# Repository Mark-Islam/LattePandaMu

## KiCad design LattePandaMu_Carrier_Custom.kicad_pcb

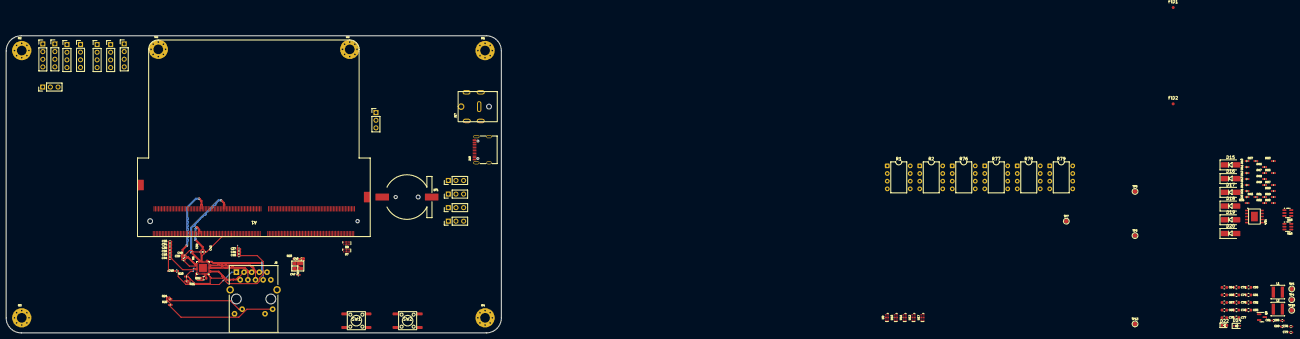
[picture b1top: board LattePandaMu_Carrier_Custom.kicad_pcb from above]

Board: 4 copper layers, 164.3 x 98.6 mm, 127 parts (0 on the bottom side), 90 nets.

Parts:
A1: LattePanda_Mu; LattePanda_Module_H8.0mm_Horizontal
BT1: Battery_Cell; Battery_Holder_CR1220_S8411-45R
C33, C34, C35, C36, C37, C38, C39, C40, C41, C42, C43, C45, C48: 100nF/50V; C_0402_1005Metric
C44: 10uF/50V; C_0402_1005Metric
C46, C47: 12pF/50V; C_0402_1005Metric
C61, C66, C69: 1uF/16V; C_0402_1005Metric
C64, C65, C67, C68, C74, C75, C76, C77, C80, C81, C82, C83: 22uF/10V; C_0603_1608Metric
C70, C71: 100nF/50V; C_0603_1608Metric
C78, C79: 100nF/16V; C_0402_1005Metric
D10, D11, D21, D25: ESD9B5.0ST5G; D_0402_1005Metric
D12, D13, D14: D_Zener; D_0402_1005Metric
D15, D16, D17, D18, D19, D20: D_Schottky; D_SMA
D22: LED; LED_0603_1608Metric
D24: 3V3 Izt=5mA; D_SOD-323
FID1, FID2: Fiducial; Fiducial_1mm_Mask2mm
H1, H2, H3, H4, H5, H6: MountingHole_Pad; MountingHole_3.2mm_M3_Pad_Via
J1, J8, J10, J11, J14: Conn_01x03_Pin; PinHeader_1x03_P2.54mm_Vertical
J6: RJ45_RB1-125B8G1A; RJ45_UDE_RB1-125B8G1A
J7, J9, J12, J13, J19, J20, J21: Conn_01x04; PinHeader_1x04_P2.54mm_Vertical
J17: Barrel_Jack_Switch; DC_Jack_DC007B_30V_10A
J18: USB_C_Receptacle_USB2.0_16P; USB_C_Receptacle_G-Switch_GT-USB-7010ASV
JP1: Jumper_3_Bridged12; PinHeader_1x03_P2.54mm_Vertical
L1, L2: 2.2uH/4.3A; L_Sunlord_SWPA4020S
Q8: 2N7002; SOT-23
R1: 1K/1%; DIP-8_W7.62mm
R2, R78, R79: 10K/1%; DIP-8_W7.62mm
R20, R21, R36, R49, R58: 10K/1%; R_0402_1005Metric
R22: 2.49K/1%; R_0603_1608Metric
R23: 1M/1%; R_0402_1005Metric
R24, R25: 470R/1%; R_0402_1005Metric
R37, R47: 1K/1%; R_0402_1005Metric
R43: 56K/1%; R_0402_1005Metric
R46, R48, R55: 100R/1%; R_0402_1005Metric
R51: 100K/1%; R_0402_1005Metric
R52, R53: 2.2K/1%; R_0402_1005Metric
R57: 75K/1%; R_0402_1005Metric
R59: 21.5K/1%; R_0402_1005Metric
R60: 4.7K/1%; R_0402_1005Metric
R76, R77: 100K/1%; DIP-8_W7.62mm
SW1, SW2: SW_Push; SW_Push_6x6x6
TP3, TP4, TP5, TP6, TP7, TP10, TP13: TestPoint; TestPoint_Pad_D1.5mm
U6: RTL8111H-CG-RH; QFN-32-1EP_4x4mm_P0.4mm_EP2.65x2.65mm
U7, U8, U9, U10, U11, U12, U17: D3V3XA4B10LP; Diodes_UDFN-10_1.0x2.5mm_P0.5mm
U14: USB PD等快充协议受电芯片-CH224K-ESSOP10; ESSOP-10-1EP_3.9x5mm_P1.0mm_EP3.2x2.3
U15, U16: LM2734X; TSOT-23-6
Y1: 25MHz; Crystal_SMD_3225-4Pin_3.2x2.5mm

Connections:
+1V0: C33.2, C34.2, C35.2, C36.2, C40.2, C44.2, U6.3 (AVDD10), U6.8 (AVDD10), U6.22 (DVDD10), U6.24 (REGOUT), U6.30 (AVDD10)
+3V3: C37.2, C41.2, C45.2, C75.2, C77.2, C79.2, C81.2, C83.2, J13.1, J13.2, J13.3, J13.4, J14.1, J14.2, J14.3, J21.1, J21.2, J21.3, J21.4, L2.2, R20.2, R21.2, R24.2, R25.2, R52.1, R59.2, TP6.1 (1_1), U6.11 (AVDD33), U6.23 (VDDREG), U6.32 (AVDD33)
+5V: C74.2, C76.2, C78.2, C82.2, L1.2, R57.2, TP5.1 (1_1)
+12V: D15.2 (A), D16.2 (A), D17.2 (A), J17.1, TP4.1 (1_1)
+15V: D12.1 (K), D18.2 (A), D19.2 (A), D20.2 (A), J18.A4 (VBUS), J18.A9 (VBUS), J18.B4 (VBUS), J18.B9 (VBUS), R36.1, R37.1, TP3.1 (1_1)
+BATT: A1.115 (VBAT), R1.2
/GPIO/GPP_D0: A1.128 (GPP_D0), J19.1, U17.1, U17.10 (NC)
/GPIO/GPP_D1: A1.130 (GPP_D1), J19.2, U17.2, U17.9 (NC)
/GPIO/GPP_D2: A1.132 (GPP_D2), J19.3, U17.4, U17.7 (NC)
/GPIO/GPP_D3: A1.134 (GPP_D3), J19.4, U17.5, U17.6 (NC)
/GPIO/I2C2_SCL: A1.154 (I2C2_SCL), J9.1, U11.1, U11.10 (NC)
/GPIO/I2C2_SDA: A1.156 (I2C2_SDA), J7.1, U9.1, U9.10 (NC)
/GPIO/I2C3_SCL: A1.150 (I2C3_SCL), J9.2, U11.2, U11.9 (NC)
/GPIO/I2C3_SDA: A1.152 (I2C3_SDA), J7.2, U9.2, U9.9 (NC)
/GPIO/I2C4_SCL: A1.146 (I2C4_SCL), J9.3, U11.4, U11.7 (NC)
/GPIO/I2C4_SDA: A1.148 (I2C4_SDA), J7.3, U9.4, U9.7 (NC)
/GPIO/I2C5_SCL: A1.142 (I2C5_SCL), J9.4, U11.5, U11.6 (NC)
/GPIO/I2C5_SDA: A1.144 (I2C5_SDA), J7.4, U9.5, U9.6 (NC)
/GPIO/SOC_UART0_RX: A1.137 (UART0_RXD), J8.1, U10.1, U10.10 (NC)
/GPIO/SOC_UART0_TX: A1.139 (UART0_TXD), J10.1, U12.1, U12.10 (NC)
/GPIO/SOC_UART1_RX: A1.141 (UART1_RXD), J8.2, U10.2, U10.9 (NC)
/GPIO/SOC_UART1_TX: A1.143 (UART1_TXD), J10.2, U12.2, U12.9 (NC)
/GPIO/SOC_UART2_RX: A1.140 (UART2_RXD), J8.3, U10.4, U10.7 (NC)
/GPIO/SOC_UART2_TX: A1.138 (UART2_TXD), J10.3, U12.4, U12.7 (NC)
/Gigabit Ethernet/GbE_PCIe_CLK+: A1.94 (REFCLK4+), U6.15 (REFCLK_P)
/Gigabit Ethernet/GbE_PCIe_CLK-: A1.96 (REFCLK4-), U6.16 (REFCLK_N)
/Gigabit Ethernet/GbE_PCIe_RX+: A1.64 (HSIO6_RX+), C43.2
/Gigabit Ethernet/GbE_PCIe_RX-: A1.66 (HSIO6_RX-), C39.2
/Gigabit Ethernet/GbE_PCIe_TX+: A1.61 (HSIO6_TX+), C42.2
/Gigabit Ethernet/GbE_PCIe_TX-: A1.63 (HSIO6_TX-), C38.2
/Gigabit Ethernet/HS0+: C43.1, U6.17 (HSOP)
/Gigabit Ethernet/HS0-: C39.1, U6.18 (HSON)
/Gigabit Ethernet/HSI+: C42.1, U6.13 (HSIP)
/Gigabit Ethernet/HSI-: C38.1, U6.14 (HSIN)
/Gigabit Ethernet/MDI0+: J6.R2 (TD1+), U6.1 (MDIP0), U7.4, U7.7 (NC)
/Gigabit Ethernet/MDI0-: J6.R3 (TD1-), U6.2 (MDIN0), U7.5, U7.6 (NC)
/Gigabit Ethernet/MDI1+: J6.R4 (TD2+), U6.4 (MDIP1), U7.1, U7.10 (NC)
/Gigabit Ethernet/MDI1-: J6.R5 (TD2-), U6.5 (MDIN1), U7.2, U7.9 (NC)
/Gigabit Ethernet/MDI2+: J6.R6 (TD3+), U6.6 (MDIP2), U8.5, U8.6 (NC)
/Gigabit Ethernet/MDI2-: J6.R7 (TD3-), U6.7 (MDIN2), U8.4, U8.7 (NC)
/Gigabit Ethernet/MDI3+: J6.R8 (TD4+), U6.9 (MDIP3), U8.2, U8.9 (NC)
/Gigabit Ethernet/MDI3-: J6.R9 (TD4-), U6.10 (MDIN3), U8.1, U8.10 (NC)
/Gigabit Ethernet/~PLT_RST: A1.105 (~PLTRST), U6.19 (PERSTB)
/LattePanda Module/SLS_S3: A1.7 (SLS_S3), JP1.3 (B)
/LattePanda Module/~PWR_LED/~PSON: A1.5 (SLS_S0), JP1.1 (A), R47.2
/LattePanda Module/~PWR_SW: A1.1 (~PWRBTN), R48.1
/LattePanda Module/~RST_SW: A1.3 (~RSTBTN), R55.1
/Power Supply/CC1: D13.1 (K), J18.A5 (CC1), U14.7 (CC1)
/Power Supply/CC2: D14.1 (K), J18.B5 (CC2), U14.6 (CC2)
/Power Supply/PWR_C_D+: D11.2 (A2), J18.A6 (D+), J18.B6 (D+), U14.4 (DP)
/Power Supply/PWR_C_D-: D10.2 (A2), J18.A7 (D-), J18.B7 (D-), U14.5 (DM)
GND: A1.11 (GND), A1.14 (GND), A1.17 (GND), A1.20 (GND), A1.23 (GND), A1.26 (GND), A1.29 (GND), A1.32 (GND), A1.35 (GND), A1.38 (GND), A1.41 (GND), A1.44 (GND), A1.47 (GND), A1.50 (GND), A1.53 (GND), A1.56 (GND), A1.59 (GND), A1.62 (GND), A1.65 (GND), A1.68 (GND), A1.71 (GND), A1.74 (GND), A1.77 (GND), A1.80 (GND), A1.83 (GND), A1.86 (GND), A1.89 (GND), A1.92 (GND), A1.95 (GND), A1.98 (GND), A1.101 (GND), A1.107 (GND), A1.110 (GND), A1.113 (GND), A1.116 (GND), A1.135 (GND), A1.136 (GND), A1.151 (GND), A1.158 (GND), A1.167 (GND), A1.170 (GND), A1.181 (GND), A1.182 (GND), A1.188 (GND), A1.189 (GND), A1.194 (GND), A1.195 (GND), A1.200 (GND), A1.201 (GND), A1.206 (GND), A1.207 (GND), A1.212 (GND), A1.213 (GND), A1.218 (GND), A1.219 (GND), A1.224 (GND), A1.225 (GND), A1.230 (GND), A1.231 (GND), A1.236 (GND), A1.237 (GND), A1.242 (GND), A1.243 (GND), A1.248 (GND), A1.249 (GND), A1.MP (Mountinge_Pads), BT1.2 (-), C33.1, C34.1, C35.1, C36.1, C37.1, C40.1, C41.1, C44.1, C45.1, C46.2, C47.2, C48.1, C61.1, C64.2, C65.1, C66.1, C67.2, C68.1, C69.1, C75.1, C77.1, C79.1, C80.1, C81.1, C82.1, C83.1, D10.1 (A1), D11.1 (A1), D12.2 (A), D13.2 (A), D14.2 (A), D21.1 (A1), D24.2 (A), D25.1 (A1), H1.1 (1_1), H2.1 (1_1), H3.1 (1_1), H4.1 (1_1), H5.1 (1_1), H6.1 (1_1), J1.3, J6.R10 (GND), J6.SH, J11.1, J11.2, J11.3, J12.1, J12.2, J12.3, J12.4, J17.2, J17.3, J18.A1 (GND), J18.A12 (GND), J18.B1 (GND), J18.B12 (GND), J20.1, J20.2, J20.3, J20.4, Q8.2 (S), R22.2, R43.2, R49.2, R51.1, R58.1, R60.1, R76.1, R77.1, R78.1, R79.1, SW1.2, SW2.2, U6.33 (GND), U7.3 (VSS), U7.8 (VSS), U8.3 (VSS), U8.8 (VSS), U9.3 (VSS), U9.8 (VSS), U10.3 (VSS), U10.8 (VSS), U11.3 (VSS), U11.8 (VSS), U12.3 (VSS), U12.8 (VSS), U14.0 (GND), U15.2 (GND), U16.2 (GND), U17.3 (VSS), U17.8 (VSS), Y1.2 (G), Y1.4 (G)
unnamed: A1.12 (SIO_UART_RX), J1.2
unnamed: A1.10 (SIO_UART_TX), J1.1
unnamed: A1.187 (TCP0_HPD), R76.2
unnamed: A1.185 (TCP1_HPD), R77.2
unnamed: A1.133 (~BIOS_SEL), R2.1, TP7.1 (1_1)
unnamed: A1.100 (~CLKREQ3), R79.2
unnamed: A1.102 (~CLKREQ4), R78.2
unnamed: BT1.1 (+), R1.1
unnamed: C66.2, D21.2 (A2), R48.2, SW1.1
unnamed: D22.2 (A), R52.2
unnamed: D22.1 (K), Q8.3 (D)
unnamed: C69.2, D25.2 (A2), R55.2, SW2.1
unnamed: C48.2, J6.R1 (CT)
unnamed: J6.L1, R25.1
unnamed: J6.L3, R24.1
unnamed: JP1.2 (C), R46.2
unnamed: Q8.1 (G), R47.1, R49.1
unnamed: C47.1, R23.1, U6.28 (CKXTAL1), Y1.1
unnamed: C46.1, R23.2, U6.29 (CKXTAL2), Y1.3
unnamed: R20.1, U6.20 (ISOLATEB)
unnamed: R21.1, U6.21 (LANWAKEB)
unnamed: J6.L4, U6.26 (LED1)
unnamed: J6.L2, U6.25 (LED2)
unnamed: R22.1, U6.31 (RSET)
unnamed: U10.5, U10.6 (NC)
unnamed: U12.5, U12.6 (NC)
unnamed: R43.1, U14.9 (CFG1)
unnamed: R36.2, U14.8 (VBUS)
unnamed: C61.2, R37.2, U14.1 (VDD)
unnamed: C70.1, U15.1 (BOOST)
unnamed: R46.1, R51.2, U15.4 (EN), U16.4 (EN)
unnamed: R57.1, R58.2, U15.3 (FB)
unnamed: C70.2, L1.1, U15.6 (SW)
unnamed: C71.1, U16.1 (BOOST)
unnamed: R59.1, R60.2, U16.3 (FB)
unnamed: C71.2, L2.1, U16.6 (SW)
VDC: A1.250 (VIN), A1.251 (VIN), A1.252 (VIN), A1.253 (VIN), A1.254 (VIN), A1.255 (VIN), A1.256 (VIN), A1.257 (VIN), A1.258 (VIN), A1.259 (VIN), A1.260 (VIN), C64.1, C65.2, C67.1, C68.2, D15.1 (K), D16.1 (K), D17.1 (K), D18.1 (K), D19.1 (K), D20.1 (K), R53.2, TP10.1 (1_1), U15.5 (VIN), U16.5 (VIN)
VPullup: D24.1 (K), R2.2, R53.1, TP13.1 (1_1)
